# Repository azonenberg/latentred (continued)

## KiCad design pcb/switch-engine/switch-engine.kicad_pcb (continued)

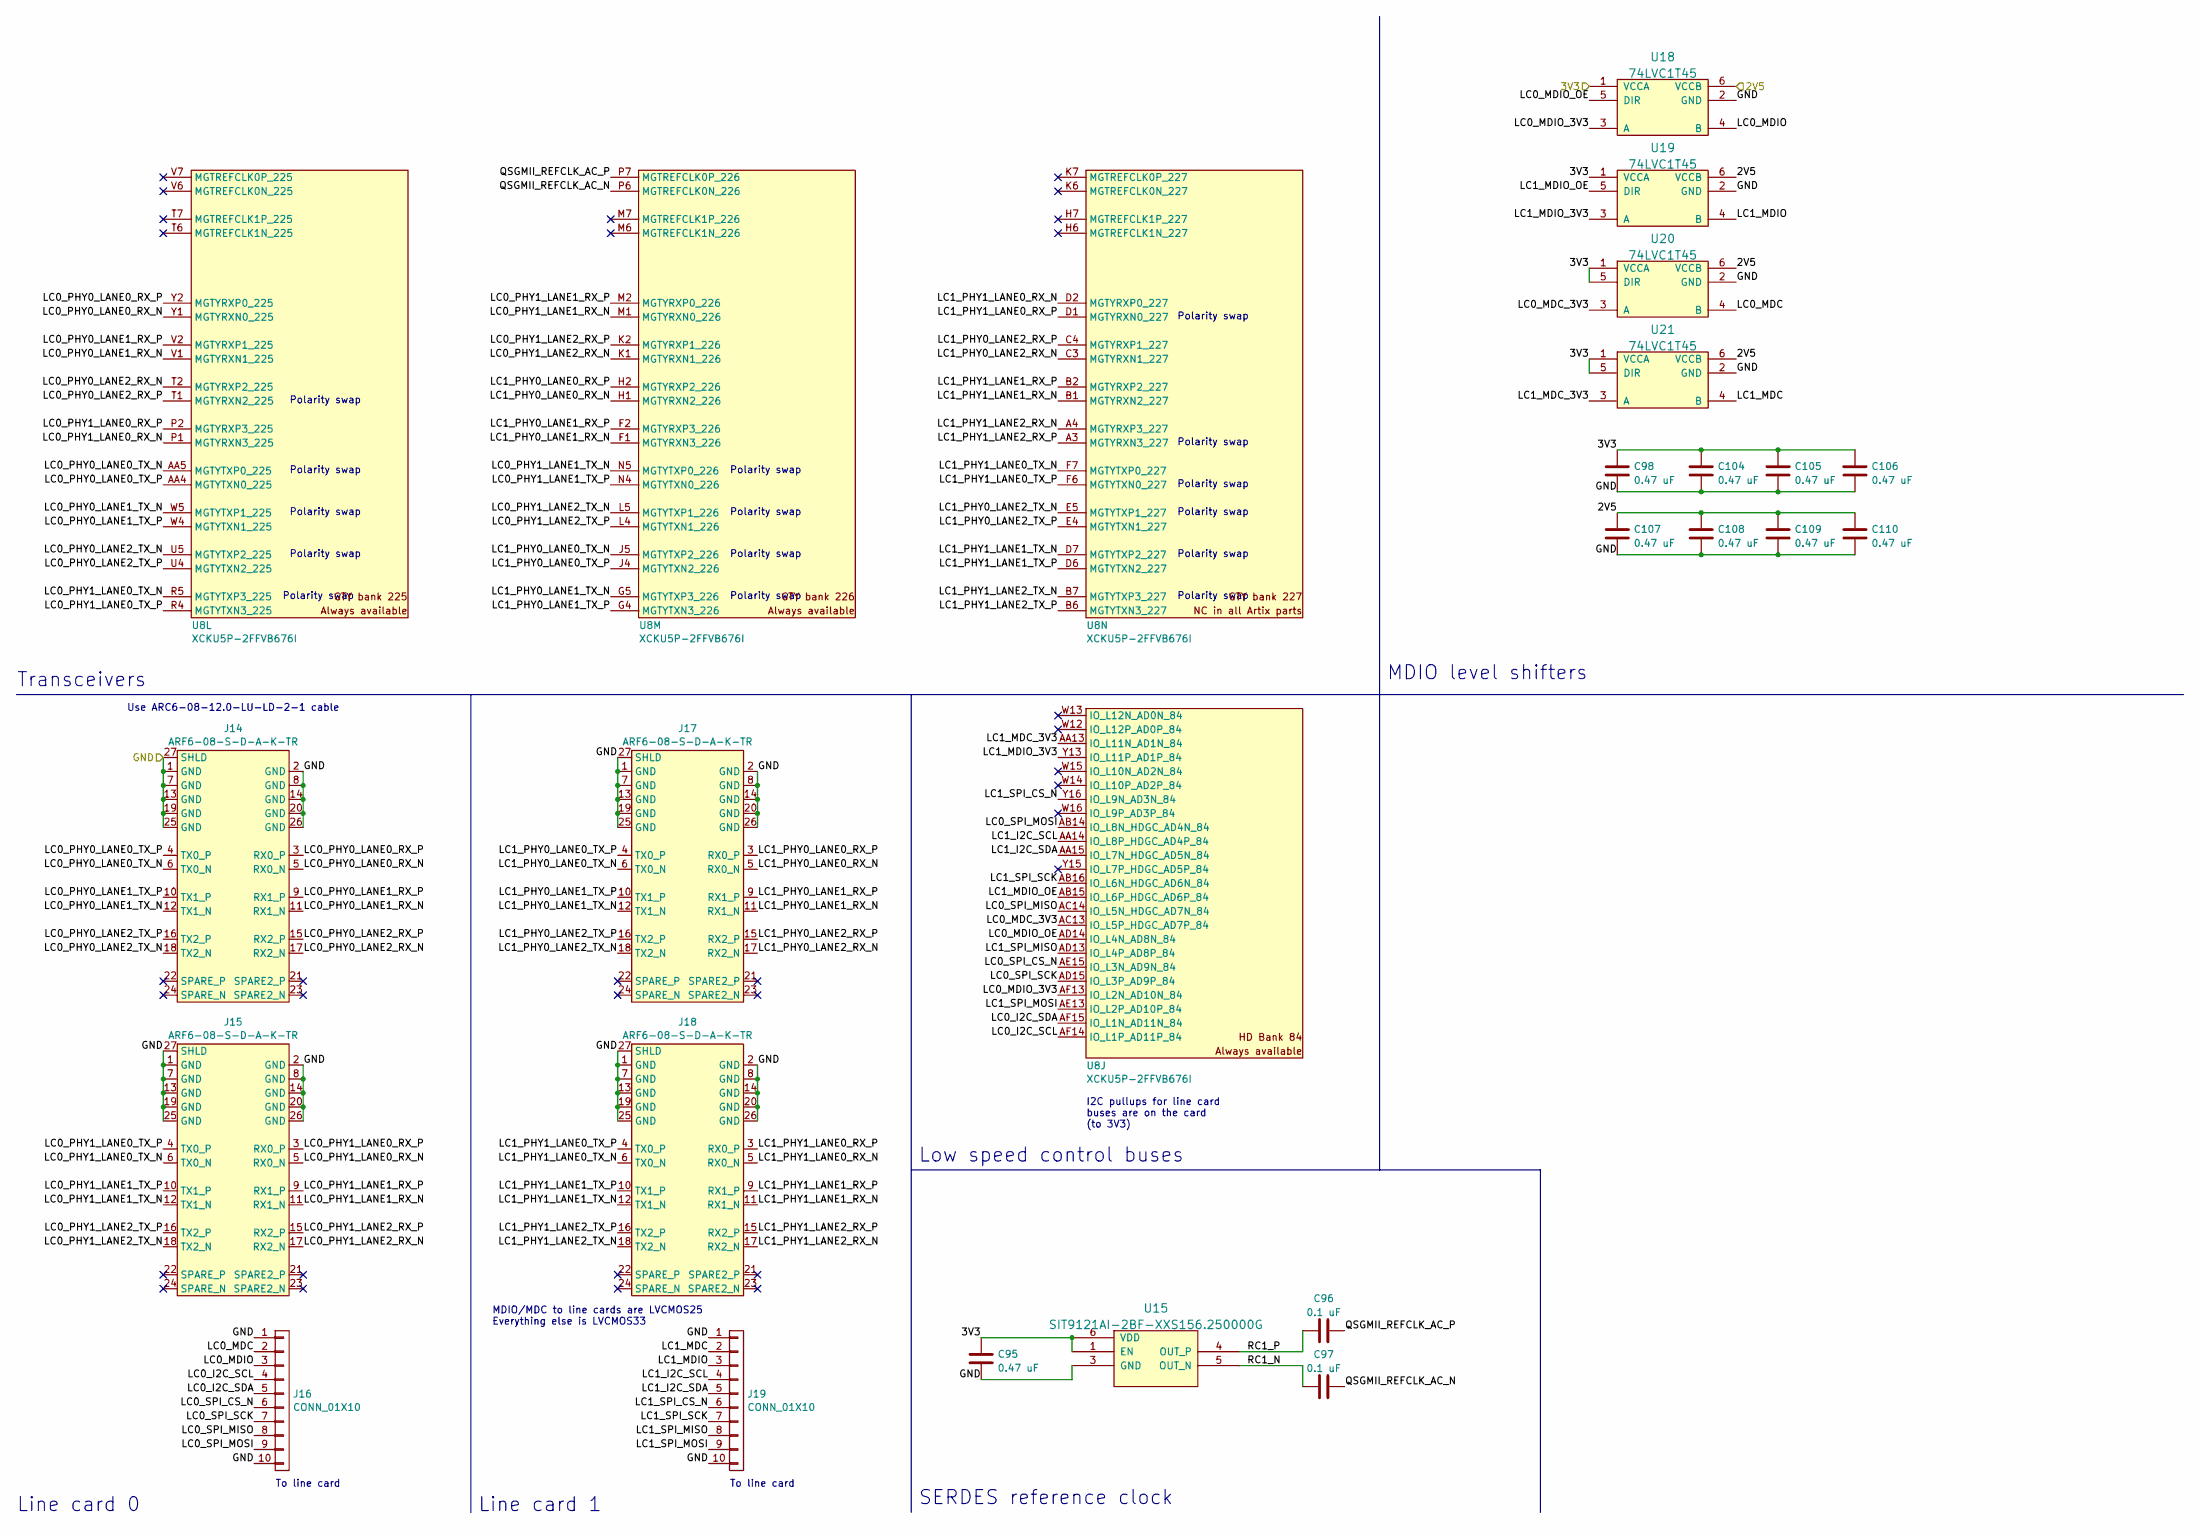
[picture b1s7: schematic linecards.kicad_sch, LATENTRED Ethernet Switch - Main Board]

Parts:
C95, C98, C104, C105, C106, C107, C108, C109, C110: 0.47 uF; EIA_0402_CAP_NOSILK
C96, C97: 0.1 uF; EIA_0402_CAP_NOSILK
J14, J15, J17, J18: ARF6-08-S-D-A-K-TR; CONN_SAMTEC_ARF6-08-S-D-A-K-TR
J16, J19: CONN_01X10; CONN_MOLEX_PICOBLADE_10POS_0532611071
U8: XCKU5P-2FFVB676I; BGA_676_27x27_FULLARRAY_1MM_FFG676
U15: SIT9121AI-2BF-XXS156.250000G; OSCILLATOR_LVDS_3.2x2.5
U18, U19, U20, U21: 74LVC1T45; DFN_6_0.5MM_1.6x1.6MM_TI_DPK

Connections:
/2V5: C107.1, C108.1, C109.1, C110.1, U18.6 (VCCB), U19.6 (VCCB), U20.6 (VCCB), U21.6 (VCCB); also elsewhere on the board
/3V3: C95.1, C98.1, C104.1, C105.1, C106.1, U15.1 (EN), U15.6 (VDD), U18.1 (VCCA), U19.1 (VCCA), U20.1 (VCCA), U20.5 (DIR), U21.1 (VCCA), U21.5 (DIR); also elsewhere on the board
/GND: C95.2, C98.2, C104.2, C105.2, C106.2, C107.2, C108.2, C109.2, C110.2, J14.1 (GND), J14.2 (GND), J14.7 (GND), J14.8 (GND), J14.13 (GND), J14.14 (GND), J14.19 (GND), J14.20 (GND), J14.25 (GND), J14.26 (GND), J14.27 (SHLD), J15.1 (GND), J15.2 (GND), J15.7 (GND), J15.8 (GND), J15.13 (GND), J15.14 (GND), J15.19 (GND), J15.20 (GND), J15.25 (GND), J15.26 (GND), J15.27 (SHLD), J16.1, J16.10, J17.1 (GND), J17.2 (GND), J17.7 (GND), J17.8 (GND), J17.13 (GND), J17.14 (GND), J17.19 (GND), J17.20 (GND), J17.25 (GND), J17.26 (GND), J17.27 (SHLD), J18.1 (GND), J18.2 (GND), J18.7 (GND), J18.8 (GND), J18.13 (GND), J18.14 (GND), J18.19 (GND), J18.20 (GND), J18.25 (GND), J18.26 (GND), J18.27 (SHLD), J19.1, J19.10, U15.3 (GND), U18.2 (GND), U19.2 (GND), U20.2 (GND), U21.2 (GND); also elsewhere on the board
/Line card interfaces/LC0_I2C_SCL: J16.4, U8.AF14 (IO_L1P_AD11P_84)
/Line card interfaces/LC0_I2C_SDA: J16.5, U8.AF15 (IO_L1N_AD11N_84)
/Line card interfaces/LC0_MDC: J16.2, U20.4 (B)
/Line card interfaces/LC0_MDC_3V3: U8.AC13 (IO_L5P_HDGC_AD7P_84), U20.3 (A)
/Line card interfaces/LC0_MDIO: J16.3, U18.4 (B)
/Line card interfaces/LC0_MDIO_3V3: U8.AF13 (IO_L2N_AD10N_84), U18.3 (A)
/Line card interfaces/LC0_MDIO_OE: U8.AD14 (IO_L4N_AD8N_84), U18.5 (DIR)
/Line card interfaces/LC0_PHY0_LANE0_RX_N: J14.5 (RX0_N), U8.Y1 (MGTYRXN0_225)
/Line card interfaces/LC0_PHY0_LANE0_RX_P: J14.3 (RX0_P), U8.Y2 (MGTYRXP0_225)
/Line card interfaces/LC0_PHY0_LANE0_TX_N: J14.6 (TX0_N), U8.AA5 (MGTYTXP0_225)
/Line card interfaces/LC0_PHY0_LANE0_TX_P: J14.4 (TX0_P), U8.AA4 (MGTYTXN0_225)
/Line card interfaces/LC0_PHY0_LANE1_RX_N: J14.11 (RX1_N), U8.V1 (MGTYRXN1_225)
/Line card interfaces/LC0_PHY0_LANE1_RX_P: J14.9 (RX1_P), U8.V2 (MGTYRXP1_225)
/Line card interfaces/LC0_PHY0_LANE1_TX_N: J14.12 (TX1_N), U8.W5 (MGTYTXP1_225)
/Line card interfaces/LC0_PHY0_LANE1_TX_P: J14.10 (TX1_P), U8.W4 (MGTYTXN1_225)
/Line card interfaces/LC0_PHY0_LANE2_RX_N: J14.17 (RX2_N), U8.T2 (MGTYRXP2_225)
/Line card interfaces/LC0_PHY0_LANE2_RX_P: J14.15 (RX2_P), U8.T1 (MGTYRXN2_225)
/Line card interfaces/LC0_PHY0_LANE2_TX_N: J14.18 (TX2_N), U8.U5 (MGTYTXP2_225)
/Line card interfaces/LC0_PHY0_LANE2_TX_P: J14.16 (TX2_P), U8.U4 (MGTYTXN2_225)
/Line card interfaces/LC0_PHY1_LANE0_RX_N: J15.5 (RX0_N), U8.P1 (MGTYRXN3_225)
/Line card interfaces/LC0_PHY1_LANE0_RX_P: J15.3 (RX0_P), U8.P2 (MGTYRXP3_225)
/Line card interfaces/LC0_PHY1_LANE0_TX_N: J15.6 (TX0_N), U8.R5 (MGTYTXP3_225)
/Line card interfaces/LC0_PHY1_LANE0_TX_P: J15.4 (TX0_P), U8.R4 (MGTYTXN3_225)
/Line card interfaces/LC0_PHY1_LANE1_RX_N: J15.11 (RX1_N), U8.M1 (MGTYRXN0_226)
/Line card interfaces/LC0_PHY1_LANE1_RX_P: J15.9 (RX1_P), U8.M2 (MGTYRXP0_226)
/Line card interfaces/LC0_PHY1_LANE1_TX_N: J15.12 (TX1_N), U8.N5 (MGTYTXP0_226)
/Line card interfaces/LC0_PHY1_LANE1_TX_P: J15.10 (TX1_P), U8.N4 (MGTYTXN0_226)
/Line card interfaces/LC0_PHY1_LANE2_RX_N: J15.17 (RX2_N), U8.K1 (MGTYRXN1_226)
/Line card interfaces/LC0_PHY1_LANE2_RX_P: J15.15 (RX2_P), U8.K2 (MGTYRXP1_226)
/Line card interfaces/LC0_PHY1_LANE2_TX_N: J15.18 (TX2_N), U8.L5 (MGTYTXP1_226)
/Line card interfaces/LC0_PHY1_LANE2_TX_P: J15.16 (TX2_P), U8.L4 (MGTYTXN1_226)
/Line card interfaces/LC0_SPI_CS_N: J16.6, U8.AE15 (IO_L3N_AD9N_84)
/Line card interfaces/LC0_SPI_MISO: J16.8, U8.AC14 (IO_L5N_HDGC_AD7N_84)
/Line card interfaces/LC0_SPI_MOSI: J16.9, U8.AB14 (IO_L8N_HDGC_AD4N_84)
/Line card interfaces/LC0_SPI_SCK: J16.7, U8.AD15 (IO_L3P_AD9P_84)
/Line card interfaces/LC1_I2C_SCL: J19.4, U8.AA14 (IO_L8P_HDGC_AD4P_84)
/Line card interfaces/LC1_I2C_SDA: J19.5, U8.AA15 (IO_L7N_HDGC_AD5N_84)
/Line card interfaces/LC1_MDC: J19.2, U21.4 (B)
/Line card interfaces/LC1_MDC_3V3: U8.AA13 (IO_L11N_AD1N_84), U21.3 (A)
/Line card interfaces/LC1_MDIO: J19.3, U19.4 (B)
/Line card interfaces/LC1_MDIO_3V3: U8.Y13 (IO_L11P_AD1P_84), U19.3 (A)
/Line card interfaces/LC1_MDIO_OE: U8.AB15 (IO_L6P_HDGC_AD6P_84), U19.5 (DIR)
/Line card interfaces/LC1_PHY0_LANE0_RX_N: J17.5 (RX0_N), U8.H1 (MGTYRXN2_226)
/Line card interfaces/LC1_PHY0_LANE0_RX_P: J17.3 (RX0_P), U8.H2 (MGTYRXP2_226)
/Line card interfaces/LC1_PHY0_LANE0_TX_N: J17.6 (TX0_N), U8.J5 (MGTYTXP2_226)
/Line card interfaces/LC1_PHY0_LANE0_TX_P: J17.4 (TX0_P), U8.J4 (MGTYTXN2_226)
/Line card interfaces/LC1_PHY0_LANE1_RX_N: J17.11 (RX1_N), U8.F1 (MGTYRXN3_226)
/Line card interfaces/LC1_PHY0_LANE1_RX_P: J17.9 (RX1_P), U8.F2 (MGTYRXP3_226)
/Line card interfaces/LC1_PHY0_LANE1_TX_N: J17.12 (TX1_N), U8.G5 (MGTYTXP3_226)
/Line card interfaces/LC1_PHY0_LANE1_TX_P: J17.10 (TX1_P), U8.G4 (MGTYTXN3_226)
/Line card interfaces/LC1_PHY0_LANE2_RX_N: J17.17 (RX2_N), U8.C3 (MGTYRXN1_227)
/Line card interfaces/LC1_PHY0_LANE2_RX_P: J17.15 (RX2_P), U8.C4 (MGTYRXP1_227)
/Line card interfaces/LC1_PHY0_LANE2_TX_N: J17.18 (TX2_N), U8.E5 (MGTYTXP1_227)
/Line card interfaces/LC1_PHY0_LANE2_TX_P: J17.16 (TX2_P), U8.E4 (MGTYTXN1_227)
/Line card interfaces/LC1_PHY1_LANE0_RX_N: J18.5 (RX0_N), U8.D2 (MGTYRXP0_227)
/Line card interfaces/LC1_PHY1_LANE0_RX_P: J18.3 (RX0_P), U8.D1 (MGTYRXN0_227)
/Line card interfaces/LC1_PHY1_LANE0_TX_N: J18.6 (TX0_N), U8.F7 (MGTYTXP0_227)
/Line card interfaces/LC1_PHY1_LANE0_TX_P: J18.4 (TX0_P), U8.F6 (MGTYTXN0_227)
/Line card interfaces/LC1_PHY1_LANE1_RX_N: J18.11 (RX1_N), U8.B1 (MGTYRXN2_227)
/Line card interfaces/LC1_PHY1_LANE1_RX_P: J18.9 (RX1_P), U8.B2 (MGTYRXP2_227)
/Line card interfaces/LC1_PHY1_LANE1_TX_N: J18.12 (TX1_N), U8.D7 (MGTYTXP2_227)
/Line card interfaces/LC1_PHY1_LANE1_TX_P: J18.10 (TX1_P), U8.D6 (MGTYTXN2_227)
/Line card interfaces/LC1_PHY1_LANE2_RX_N: J18.17 (RX2_N), U8.A4 (MGTYRXP3_227)
/Line card interfaces/LC1_PHY1_LANE2_RX_P: J18.15 (RX2_P), U8.A3 (MGTYRXN3_227)
/Line card interfaces/LC1_PHY1_LANE2_TX_N: J18.18 (TX2_N), U8.B7 (MGTYTXP3_227)
/Line card interfaces/LC1_PHY1_LANE2_TX_P: J18.16 (TX2_P), U8.B6 (MGTYTXN3_227)
/Line card interfaces/LC1_SPI_CS_N: J19.6, U8.Y16 (IO_L9N_AD3N_84)
/Line card interfaces/LC1_SPI_MISO: J19.8, U8.AD13 (IO_L4P_AD8P_84)
/Line card interfaces/LC1_SPI_MOSI: J19.9, U8.AE13 (IO_L2P_AD10P_84)
/Line card interfaces/LC1_SPI_SCK: J19.7, U8.AB16 (IO_L6N_HDGC_AD6N_84)
/Line card interfaces/QSGMII_REFCLK_AC_N: C97.2, U8.P6 (MGTREFCLK0N_226)
/Line card interfaces/QSGMII_REFCLK_AC_P: C96.2, U8.P7 (MGTREFCLK0P_226)
/Line card interfaces/RC1_N: C97.1, U15.5 (OUT_N)
/Line card interfaces/RC1_P: C96.1, U15.4 (OUT_P)

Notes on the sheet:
Polarity swap
SERDES reference clock
Line card 0
Transceivers
I2C pullups for line card buses are on the card (to 3V3)
MDIO level shifters
Low speed control buses
Line card 1
To line card
Use ARC6-08-12.0-LU-LD-2-1 cable
MDIO/MDC to line cards are LVCMOS25 Everything else is LVCMOS33

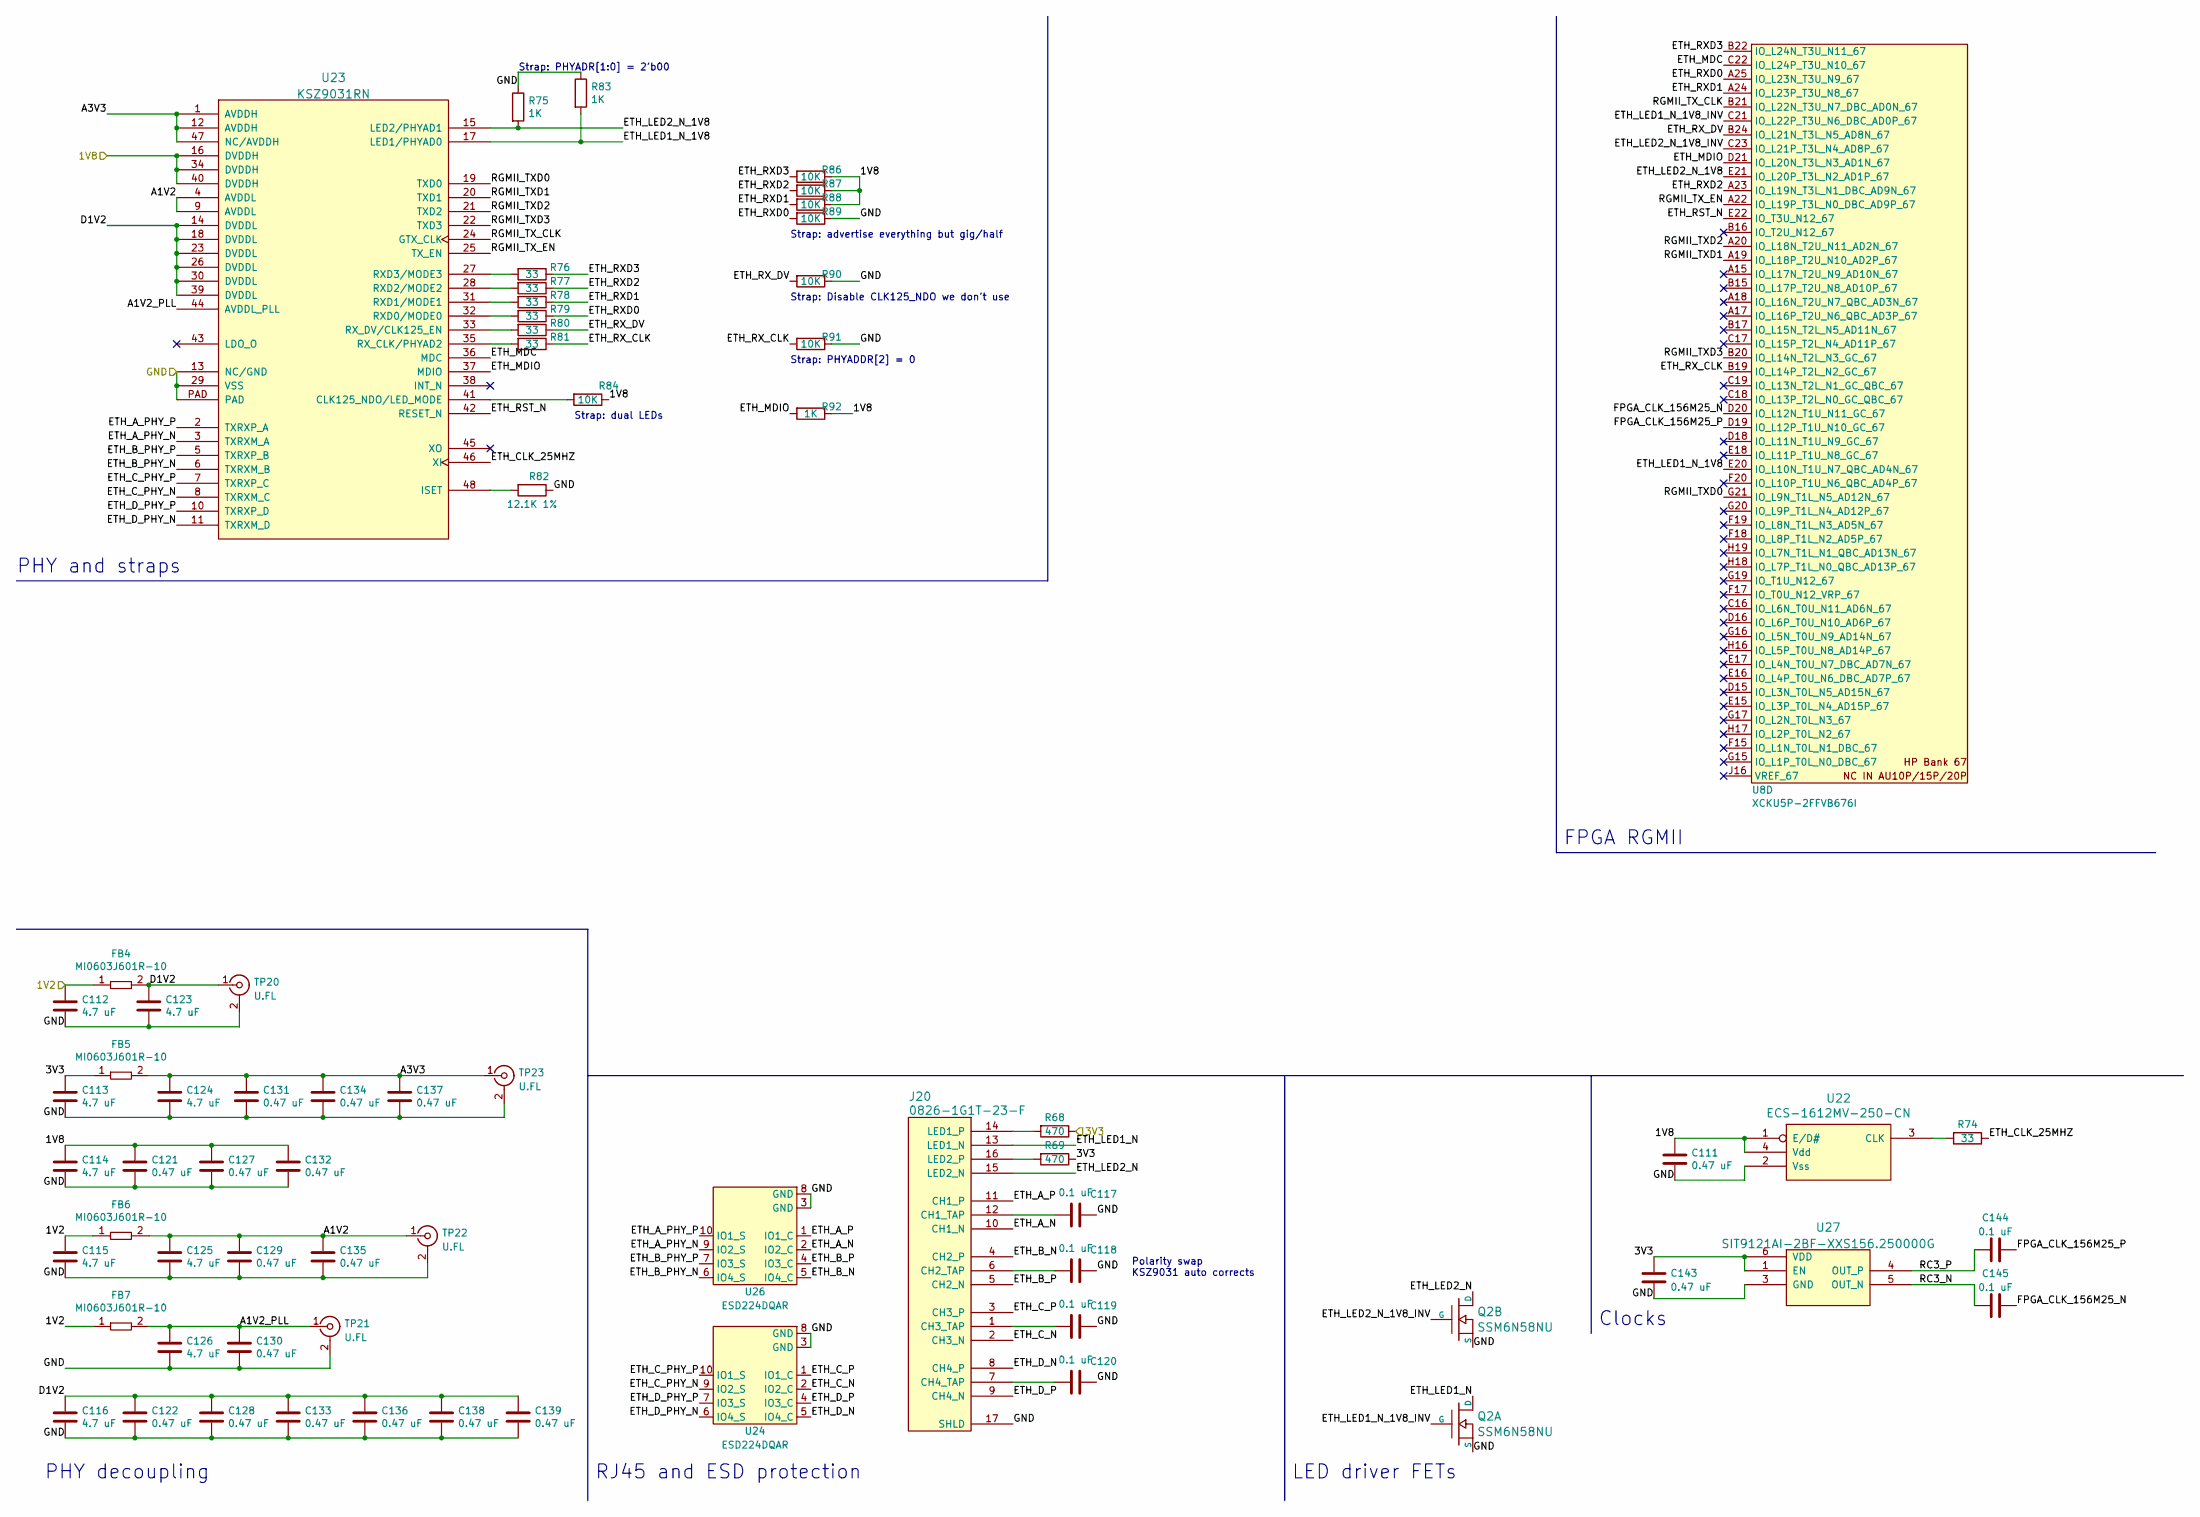
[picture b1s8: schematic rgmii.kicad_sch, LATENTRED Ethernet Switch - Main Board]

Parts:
C111, C121, C122, C127, C128, C129, C130, C131, C132, C133, C134, C135, C136, C137, C138, C139, C143: 0.47 uF; EIA_0402_CAP_NOSILK
C112, C113, C114, C115, C116, C123, C124, C125, C126: 4.7 uF; EIA_0603_CAP_NOSILK
C117, C118, C119, C120, C144, C145: 0.1 uF; EIA_0402_CAP_NOSILK
FB4, FB5, FB6, FB7: MI0603J601R-10; EIA_0603_INDUCTOR_NOSILK
J20: 0826-1G1T-23-F; CONN_BELFUSE_0826_1G1T_23_F
Q2: SSM6N58NU; DFN_6_0.65MM_2x2MM_GDS
R68, R69: 470; EIA_0402_RES_NOSILK
R74, R76, R77, R78, R79, R80, R81: 33; EIA_0402_RES_NOSILK
R75, R83, R92: 1K; EIA_0402_RES_NOSILK
R82: 12.1K 1%; EIA_0402_RES_NOSILK
R84, R86, R87, R88, R89, R90, R91: 10K; EIA_0402_RES_NOSILK
TP20, TP21, TP22, TP23: U.FL; CONN_U.FL_TE_1909763-1
U8: XCKU5P-2FFVB676I; BGA_676_27x27_FULLARRAY_1MM_FFG676
U22: ECS-1612MV-250-CN; OSCILLATOR_1.6x1.2
U23: KSZ9031RN; QFN_48_0.5MM_7x7MM
U24, U26: ESD224DQAR; DFN_10_0.5MM_2.5x1MM_TI_DQA
U27: SIT9121AI-2BF-XXS156.250000G; OSCILLATOR_LVDS_3.2x2.5

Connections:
/1V8: C111.1, C114.1, C121.1, C127.1, C132.1, R84.1, R86.1, R87.1, R88.1, R92.1, U22.1 (E/D#), U22.4 (Vdd), U23.16 (DVDDH), U23.34 (DVDDH), U23.40 (DVDDH); also elsewhere on the board
/3V3: C113.1, C143.1, FB5.1, R68.1, R69.1, U27.1 (EN), U27.6 (VDD); also elsewhere on the board
/GND: C111.2, C112.2, C113.2, C114.2, C115.2, C116.2, C117.1, C118.1, C119.1, C120.1, C121.2, C122.2, C123.2, C124.2, C125.2, C126.2, C127.2, C128.2, C129.2, C130.2, C131.2, C132.2, C133.2, C134.2, C135.2, C136.2, C137.2, C138.2, C139.2, C143.2, J20.17 (SHLD), Q2.S1 (S), Q2.S2 (S), R75.1, R82.1, R83.1, R89.1, R90.1, R91.1, TP20.2 (Ext), TP21.2 (Ext), TP22.2 (Ext), TP23.2 (Ext), U22.2 (Vss), U23.13 (NC/GND), U23.29 (VSS), U23.PAD, U24.3 (GND), U24.8 (GND), U26.3 (GND), U26.8 (GND), U27.3 (GND); also elsewhere on the board
/GTY_VTT: C112.1, C115.1, FB4.1, FB6.1, FB7.1; also elsewhere on the board
/RGMII PHY/A1V2: C125.1, C129.1, C135.1, FB6.2, TP22.1 (In), U23.4 (AVDDL), U23.9 (AVDDL)
/RGMII PHY/A1V2_PLL: C126.1, C130.1, FB7.2, TP21.1 (In), U23.44 (AVDDL_PLL)
/RGMII PHY/A3V3: C124.1, C131.1, C134.1, C137.1, FB5.2, TP23.1 (In), U23.1 (AVDDH), U23.12 (AVDDH), U23.47 (NC/AVDDH)
/RGMII PHY/D1V2: C116.1, C122.1, C123.1, C128.1, C133.1, C136.1, C138.1, C139.1, FB4.2, TP20.1 (In), U23.14 (DVDDL), U23.18 (DVDDL), U23.23 (DVDDL), U23.26 (DVDDL), U23.30 (DVDDL), U23.39 (DVDDL)
/RGMII PHY/ETH_A_N: J20.10 (CH1_N), U26.2 (IO2_C)
/RGMII PHY/ETH_A_P: J20.11 (CH1_P), U26.1 (IO1_C)
/RGMII PHY/ETH_A_PHY_N: U23.3 (TXRXM_A), U26.9 (IO2_S)
/RGMII PHY/ETH_A_PHY_P: U23.2 (TXRXP_A), U26.10 (IO1_S)
/RGMII PHY/ETH_B_N: J20.4 (CH2_P), U26.5 (IO4_C)
/RGMII PHY/ETH_B_P: J20.5 (CH2_N), U26.4 (IO3_C)
/RGMII PHY/ETH_B_PHY_N: U23.6 (TXRXM_B), U26.6 (IO4_S)
/RGMII PHY/ETH_B_PHY_P: U23.5 (TXRXP_B), U26.7 (IO3_S)
/RGMII PHY/ETH_CLK_25MHZ: R74.1, U23.46 (XI)
/RGMII PHY/ETH_C_N: J20.2 (CH3_N), U24.2 (IO2_C)
/RGMII PHY/ETH_C_P: J20.3 (CH3_P), U24.1 (IO1_C)
/RGMII PHY/ETH_C_PHY_N: U23.8 (TXRXM_C), U24.9 (IO2_S)
/RGMII PHY/ETH_C_PHY_P: U23.7 (TXRXP_C), U24.10 (IO1_S)
/RGMII PHY/ETH_D_N: J20.8 (CH4_P), U24.5 (IO4_C)
/RGMII PHY/ETH_D_P: J20.9 (CH4_N), U24.4 (IO3_C)
/RGMII PHY/ETH_D_PHY_N: U23.11 (TXRXM_D), U24.6 (IO4_S)
/RGMII PHY/ETH_D_PHY_P: U23.10 (TXRXP_D), U24.7 (IO3_S)
/RGMII PHY/ETH_LED1_N: J20.13 (LED1_N), Q2.D1 (D)
/RGMII PHY/ETH_LED1_N_1V8: R83.2, U8.E20 (IO_L10N_T1U_N7_QBC_AD4N_67), U23.17 (LED1/PHYAD0)
/RGMII PHY/ETH_LED1_N_1V8_INV: Q2.G1 (G), U8.C21 (IO_L22P_T3U_N6_DBC_AD0P_67)
/RGMII PHY/ETH_LED2_N: J20.15 (LED2_N), Q2.D2 (D)
/RGMII PHY/ETH_LED2_N_1V8: R75.2, U8.E21 (IO_L20P_T3L_N2_AD1P_67), U23.15 (LED2/PHYAD1)
/RGMII PHY/ETH_LED2_N_1V8_INV: Q2.G2 (G), U8.C23 (IO_L21P_T3L_N4_AD8P_67)
/RGMII PHY/ETH_MDC: U8.C22 (IO_L24P_T3U_N10_67), U23.36 (MDC)
/RGMII PHY/ETH_MDIO: R92.2, U8.D21 (IO_L20N_T3L_N3_AD1N_67), U23.37 (MDIO)
/RGMII PHY/ETH_RST_N: U8.E22 (IO_T3U_N12_67), U23.42 (RESET_N)
/RGMII PHY/ETH_RXD0: R79.1, R89.2, U8.A25 (IO_L23N_T3U_N9_67)
/RGMII PHY/ETH_RXD1: R78.1, R88.2, U8.A24 (IO_L23P_T3U_N8_67)
/RGMII PHY/ETH_RXD2: R77.1, R87.2, U8.A23 (IO_L19N_T3L_N1_DBC_AD9N_67)
/RGMII PHY/ETH_RXD3: R76.1, R86.2, U8.B22 (IO_L24N_T3U_N11_67)
/RGMII PHY/ETH_RX_CLK: R81.1, R91.2, U8.B19 (IO_L14P_T2L_N2_GC_67)
/RGMII PHY/ETH_RX_DV: R80.1, R90.2, U8.B24 (IO_L21N_T3L_N5_AD8N_67)
/RGMII PHY/FPGA_CLK_156M25_N: C145.2, U8.D20 (IO_L12N_T1U_N11_GC_67)
/RGMII PHY/FPGA_CLK_156M25_P: C144.2, U8.D19 (IO_L12P_T1U_N10_GC_67)
/RGMII PHY/RC3_N: C145.1, U27.5 (OUT_N)
/RGMII PHY/RC3_P: C144.1, U27.4 (OUT_P)
/RGMII PHY/RGMII_TXD0: U8.G21 (IO_L9N_T1L_N5_AD12N_67), U23.19 (TXD0)
/RGMII PHY/RGMII_TXD1: U8.A19 (IO_L18P_T2U_N10_AD2P_67), U23.20 (TXD1)
/RGMII PHY/RGMII_TXD2: U8.A20 (IO_L18N_T2U_N11_AD2N_67), U23.21 (TXD2)
/RGMII PHY/RGMII_TXD3: U8.B20 (IO_L14N_T2L_N3_GC_67), U23.22 (TXD3)
/RGMII PHY/RGMII_TX_CLK: U8.B21 (IO_L22N_T3U_N7_DBC_AD0N_67), U23.24 (GTX_CLK)
/RGMII PHY/RGMII_TX_EN: U8.A22 (IO_L19P_T3L_N0_DBC_AD9P_67), U23.25 (TX_EN)
unnamed: C117.2, J20.12 (CH1_TAP)
unnamed: C118.2, J20.6 (CH2_TAP)
unnamed: C119.2, J20.1 (CH3_TAP)
unnamed: C120.2, J20.7 (CH4_TAP)
unnamed: J20.14 (LED1_P), R68.2
unnamed: J20.16 (LED2_P), R69.2
unnamed: R74.2, U22.3 (CLK)
unnamed: R84.2, U23.41 (CLK125_NDO/LED_MODE)
unnamed: R82.2, U23.48 (ISET)
unnamed: R79.2, U23.32 (RXD0/MODE0)
unnamed: R78.2, U23.31 (RXD1/MODE1)
unnamed: R77.2, U23.28 (RXD2/MODE2)
unnamed: R76.2, U23.27 (RXD3/MODE3)
unnamed: R81.2, U23.35 (RX_CLK/PHYAD2)
unnamed: R80.2, U23.33 (RX_DV/CLK125_EN)

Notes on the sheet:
Strap: PHYADDR[2] = 0
Strap: advertise everything but gig/half
Strap: PHYADR[1:0] = 2'b00
Strap: dual LEDs
RJ45 and ESD protection
Polarity swap KSZ9031 auto corrects
LED driver FETs
PHY and straps
FPGA RGMII
Clocks
PHY decoupling
Strap: Disable CLK125_NDO we don't use

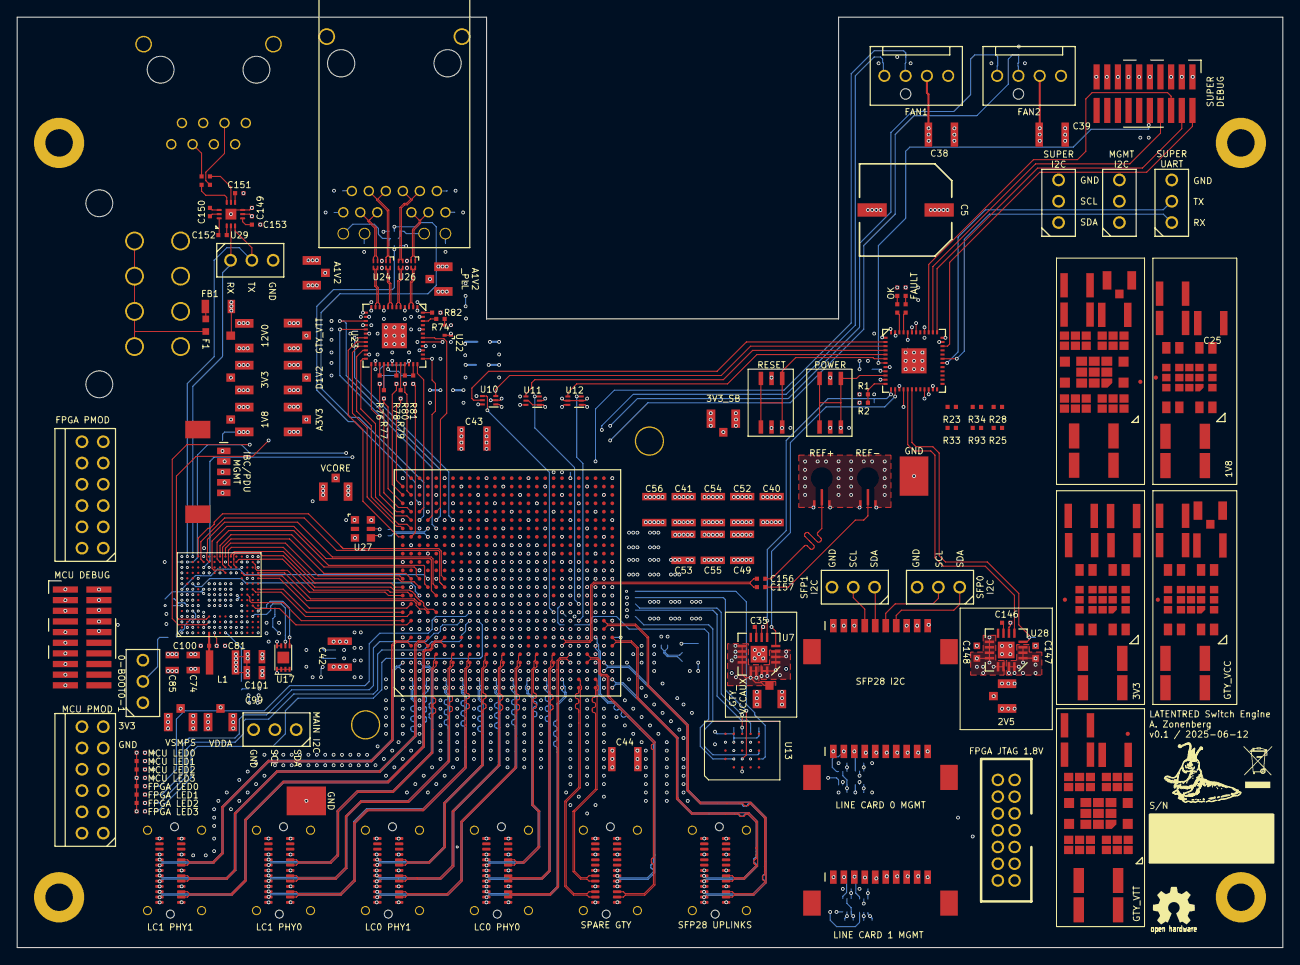
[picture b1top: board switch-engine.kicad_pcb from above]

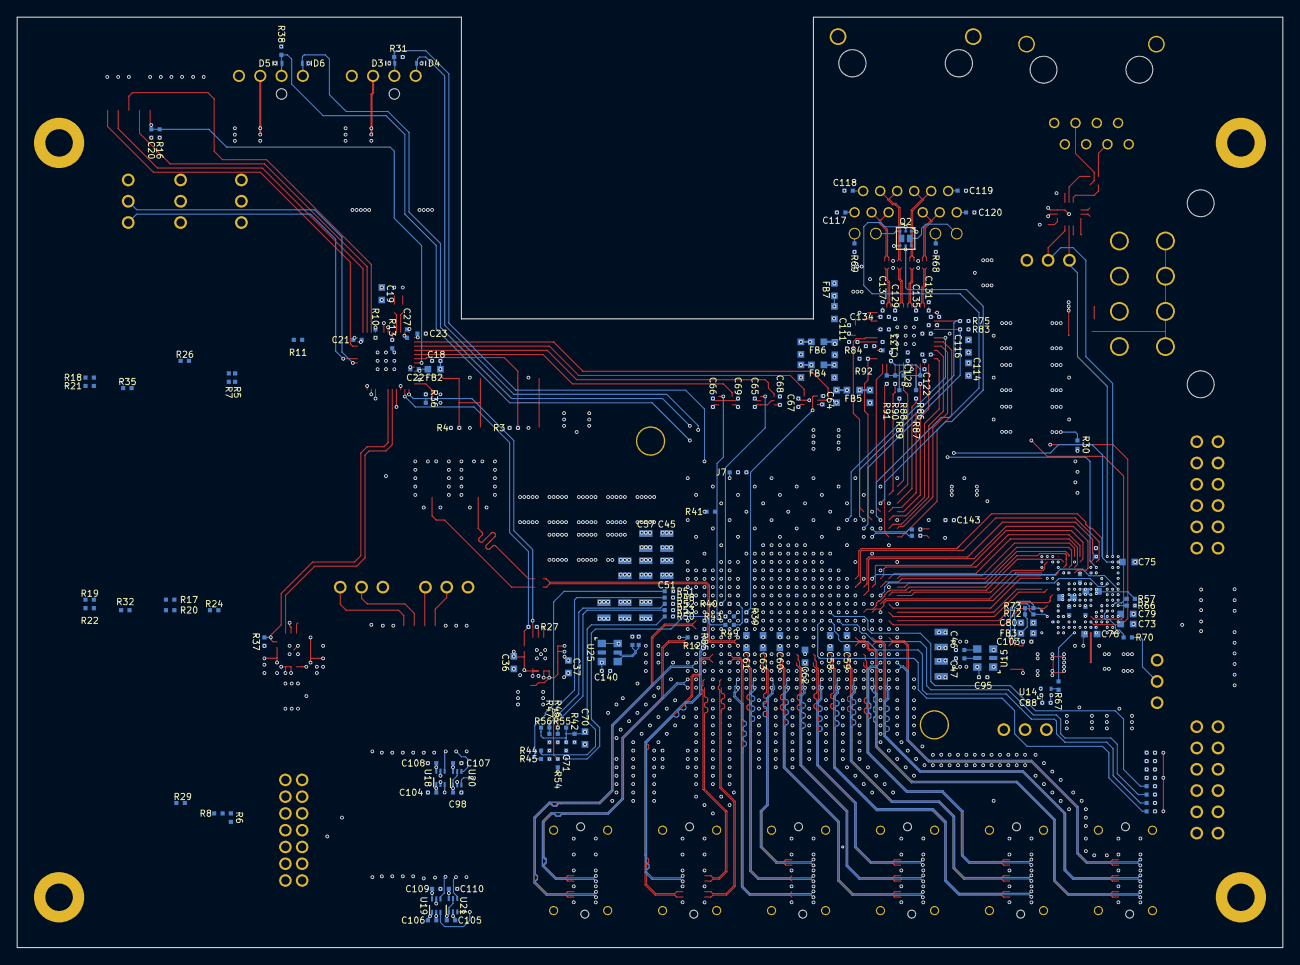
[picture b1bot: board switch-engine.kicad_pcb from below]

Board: 10 copper layers, 151.0 x 111.0 mm, 369 parts (194 on the bottom side), 358 nets.

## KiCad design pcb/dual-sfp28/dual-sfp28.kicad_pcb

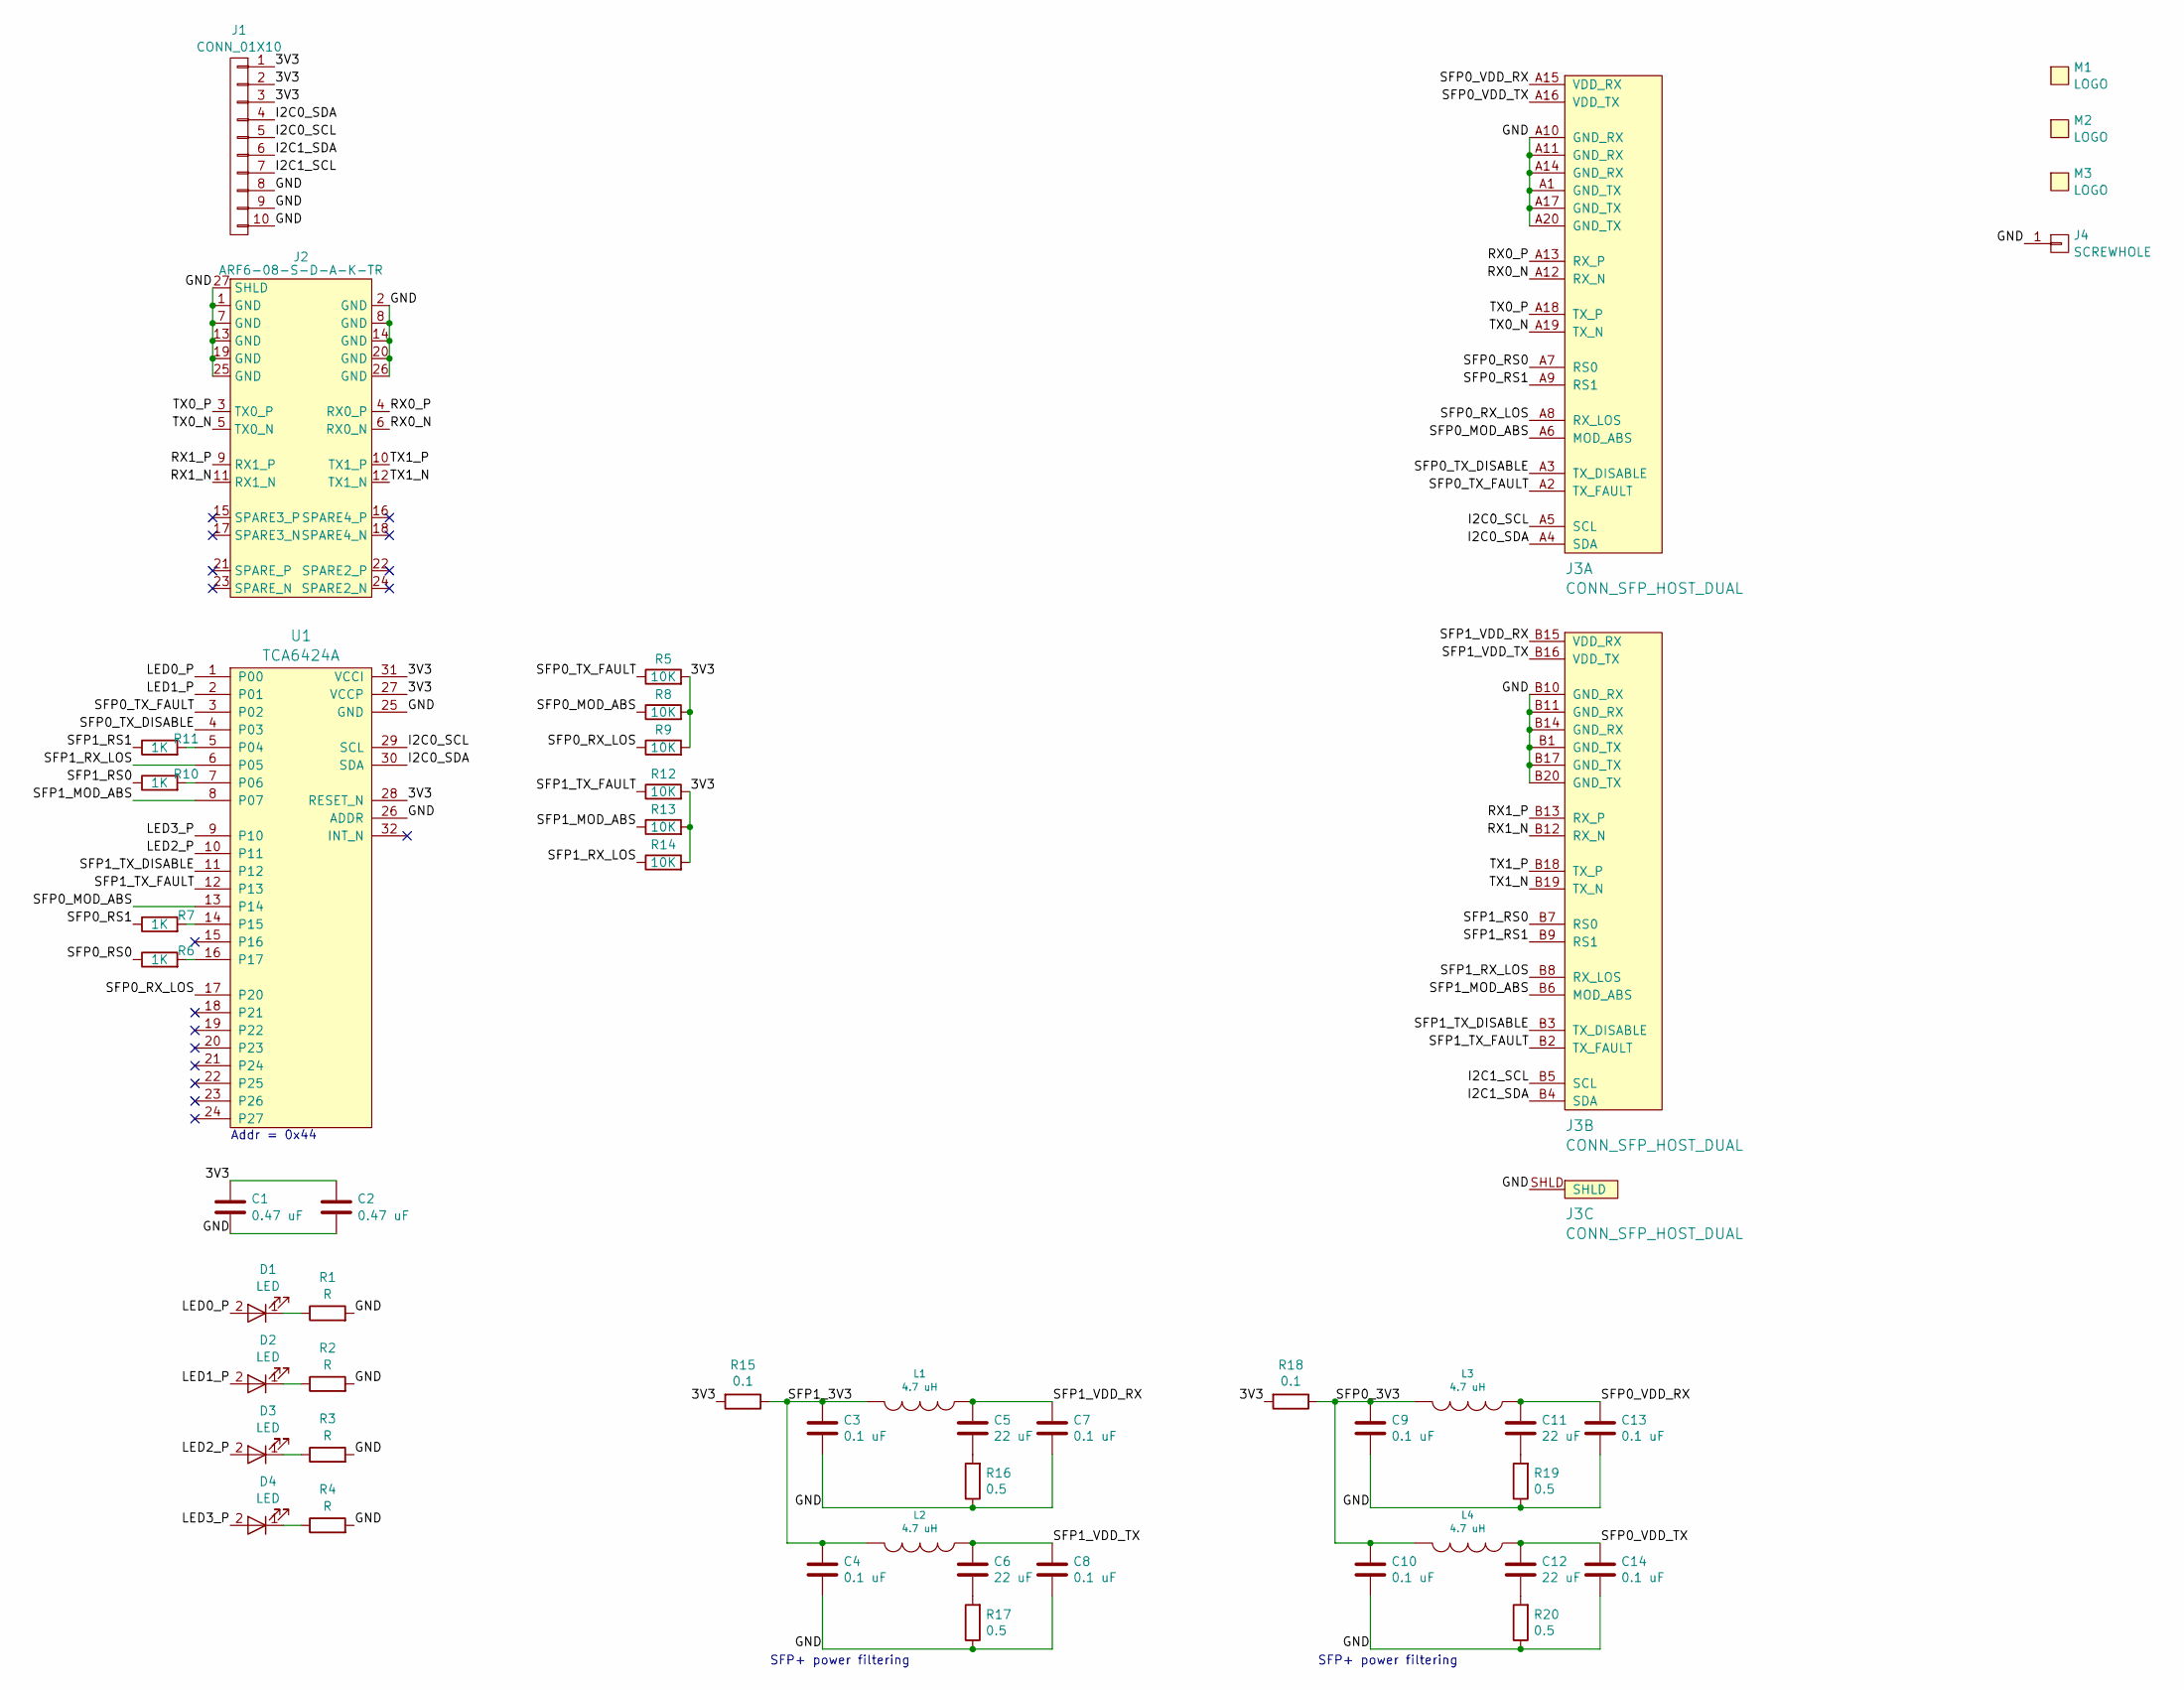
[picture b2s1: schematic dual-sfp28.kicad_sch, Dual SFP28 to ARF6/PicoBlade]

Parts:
C1, C2: 0.47 uF; EIA_0402_CAP_NOSILK
C3, C4, C7, C8, C9, C10, C13, C14: 0.1 uF; EIA_0402_CAP_NOSILK
C5, C6, C11, C12: 22 uF; EIA_0805_CAP_NOSILK
D1, D2, D3, D4: LED; EIA_0402_LED
J1: CONN_01X10; CONN_MOLEX_PICOBLADE_10POS_0532611071
J2: ARF6-08-S-D-A-K-TR; CONN_SAMTEC_ARF6-08-S-D-A-K-TR
J3: CONN_SFP_HOST_DUAL; CONN_ZSFP_DUAL_MOLEX_1712241011
J4: SCREWHOLE; MECHANICAL_CLEARANCEHOLE_4_40
L1, L2, L3, L4: 4.7 uH; EIA_0805_INDUCTOR_NOSILK
M1: LOGO; LONGTHING-1200DPI
M2: LOGO; Logo_silk_OSHW_6x6mm
M3: LOGO; Logo_silk_WEEE_3.4x5mm
R1, R2, R3, R4: R; EIA_0402_RES_NOSILK
R5, R8, R9, R12, R13, R14: 10K; EIA_0402_RES_NOSILK
R6, R7, R10, R11: 1K; EIA_0402_RES_NOSILK
R15, R18: 0.1; EIA_0402_RES_NOSILK
R16, R17, R19, R20: 0.5; EIA_0402_RES_NOSILK
U1: TCA6424A; QFN_32_0.5MM_5x5MM

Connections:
/3V3: C1.1, C2.1, J1.1, J1.2, J1.3, R5.2, R8.2, R9.2, R12.2, R13.2, R14.2, R15.2, R18.2, U1.27 (VCCP), U1.28 (RESET_N), U1.31 (VCCI)
/GND: C1.2, C2.2, C3.2, C4.2, C7.2, C8.2, C9.2, C10.2, C13.2, C14.2, J1.8, J1.9, J1.10, J2.1 (GND), J2.2 (GND), J2.7 (GND), J2.8 (GND), J2.13 (GND), J2.14 (GND), J2.19 (GND), J2.20 (GND), J2.25 (GND), J2.26 (GND), J2.27 (SHLD), J3.A1 (GND_TX), J3.A10 (GND_RX), J3.A11 (GND_RX), J3.A14 (GND_RX), J3.A17 (GND_TX), J3.A20 (GND_TX), J3.B1 (GND_TX), J3.B10 (GND_RX), J3.B11 (GND_RX), J3.B14 (GND_RX), J3.B17 (GND_TX), J3.B20 (GND_TX), J3.SHLD, J4.1, R1.2, R2.2, R3.2, R4.2, R16.1, R17.1, R19.1, R20.1, U1.25 (GND), U1.26 (ADDR)
/I2C0_SCL: J1.5, J3.A5 (SCL), U1.29 (SCL)
/I2C0_SDA: J1.4, J3.A4 (SDA), U1.30 (SDA)
/I2C1_SCL: J1.7, J3.B5 (SCL)
/I2C1_SDA: J1.6, J3.B4 (SDA)
/LED0_P: D1.2 (A), U1.1 (P00)
/LED1_P: D2.2 (A), U1.2 (P01)
/LED2_P: D3.2 (A), U1.10 (P11)
/LED3_P: D4.2 (A), U1.9 (P10)
/RX0_N: J2.6 (RX0_N), J3.A12 (RX_N)
/RX0_P: J2.4 (RX0_P), J3.A13 (RX_P)
/RX1_N: J2.11 (RX1_N), J3.B12 (RX_N)
/RX1_P: J2.9 (RX1_P), J3.B13 (RX_P)
/SFP0_3V3: C9.1, C10.1, L3.2, L4.2, R18.1
/SFP0_MOD_ABS: J3.A6 (MOD_ABS), R8.1, U1.13 (P14)
/SFP0_RS0: J3.A7 (RS0), R6.1
/SFP0_RS1: J3.A9 (RS1), R7.1
/SFP0_RX_LOS: J3.A8 (RX_LOS), R9.1, U1.17 (P20)
/SFP0_TX_DISABLE: J3.A3 (TX_DISABLE), U1.4 (P03)
/SFP0_TX_FAULT: J3.A2 (TX_FAULT), R5.1, U1.3 (P02)
/SFP0_VDD_RX: C11.1, C13.1, J3.A15 (VDD_RX), L3.1
/SFP0_VDD_TX: C12.1, C14.1, J3.A16 (VDD_TX), L4.1
/SFP1_3V3: C3.1, C4.1, L1.2, L2.2, R15.1
/SFP1_MOD_ABS: J3.B6 (MOD_ABS), R13.1, U1.8 (P07)
/SFP1_RS0: J3.B7 (RS0), R10.1
/SFP1_RS1: J3.B9 (RS1), R11.1
/SFP1_RX_LOS: J3.B8 (RX_LOS), R14.1, U1.6 (P05)
/SFP1_TX_DISABLE: J3.B3 (TX_DISABLE), U1.11 (P12)
/SFP1_TX_FAULT: J3.B2 (TX_FAULT), R12.1, U1.12 (P13)
/SFP1_VDD_RX: C5.1, C7.1, J3.B15 (VDD_RX), L1.1
/SFP1_VDD_TX: C6.1, C8.1, J3.B16 (VDD_TX), L2.1
/TX0_N: J2.5 (TX0_N), J3.A19 (TX_N)
/TX0_P: J2.3 (TX0_P), J3.A18 (TX_P)
/TX1_N: J2.12 (TX1_N), J3.B19 (TX_N)
/TX1_P: J2.10 (TX1_P), J3.B18 (TX_P)
unnamed: C5.2, R16.2
unnamed: C6.2, R17.2
unnamed: C11.2, R19.2
unnamed: C12.2, R20.2
unnamed: D1.1 (K), R1.1
unnamed: D2.1 (K), R2.1
unnamed: D3.1 (K), R3.1
unnamed: D4.1 (K), R4.1
unnamed: R11.2, U1.5 (P04)
unnamed: R10.2, U1.7 (P06)
unnamed: R7.2, U1.14 (P15)
unnamed: R6.2, U1.16 (P17)

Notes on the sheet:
SFP+ power filtering
Addr = 0x44
